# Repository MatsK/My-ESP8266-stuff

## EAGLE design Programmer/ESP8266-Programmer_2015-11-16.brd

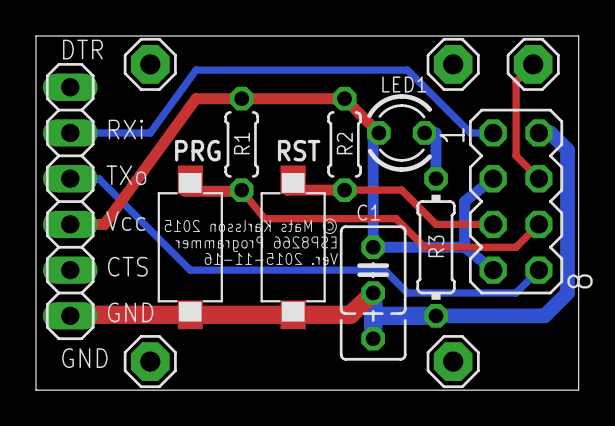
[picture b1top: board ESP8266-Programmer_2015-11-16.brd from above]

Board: 2 copper layers, 30.1 x 19.7 mm, 14 parts (0 on the bottom side), 8 nets.

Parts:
C1: C025_050-035X075
JP1: 1X06
LED1: TLLG4400; LED3MM
LSP1, LSP2, LSP3, LSP5, LSP6: SE11
PRG: KSS-2EG4430
R1, R2: 0204/5
R3: 0204/7
RST: KSS-2EG4430
SV1: MA04-2

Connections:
unnamed: C1.2, JP1.1, PRG.1, R3.1, RST.1, SV1.2
unnamed: R2.1, RST.2, SV1.5
unnamed: LSP3.MP, SV1.4
unnamed: JP1.4, SV1.8
unnamed: PRG.2, R1.1, SV1.6
unnamed: C1.1, JP1.3, LED1.A, R1.2, R2.2, SV1.3, SV1.7
unnamed: JP1.5, SV1.1
unnamed: LED1.K, R3.2

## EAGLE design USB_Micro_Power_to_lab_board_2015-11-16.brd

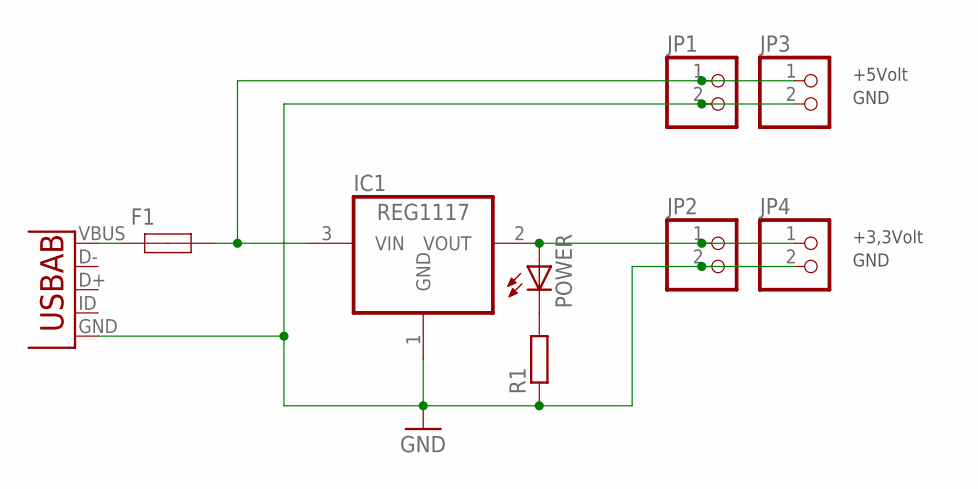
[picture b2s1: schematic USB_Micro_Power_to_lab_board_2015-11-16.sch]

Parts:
F1: LITTELFUSE_1812_500MA; R1812
IC1: REG1117; SOT223
JP1, JP2, JP3, JP4: PINHD-1X2; 1X02
POWER: LED3MM
R1: R-EU_0204/5; 0204/5
U1: USB-ABUSB-AB-MICRO-SMD; USB-AB-MICRO-SMD_VO2

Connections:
GND: IC1.1 (GND), JP1.2, JP2.2, JP3.2, JP4.2, R1.1, U1.GND
unnamed: F1.2, IC1.3 (VIN), JP1.1, JP3.1
unnamed: F1.1, U1.VBUS
unnamed: POWER.K (C), R1.2
unnamed: IC1.2 (VOUT), JP2.1, JP4.1, POWER.A

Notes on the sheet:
GND
+3,3Volt
+5Volt

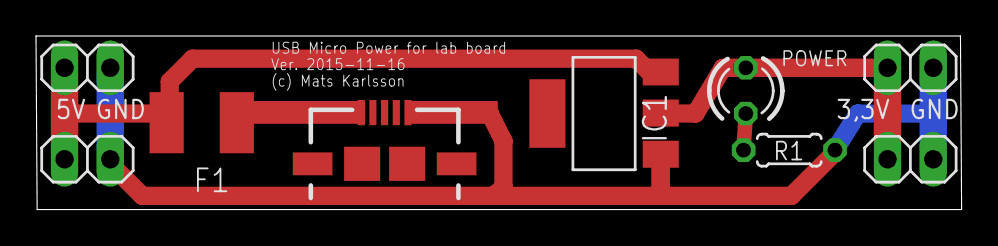
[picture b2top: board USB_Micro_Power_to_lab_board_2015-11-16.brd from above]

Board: 2 copper layers, 51.4 x 9.6 mm, 9 parts (0 on the bottom side), 5 nets.

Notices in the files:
Programmer/ESP8266-Programmer_2015-11-16.brd:
© Mats Karlsson 2015
